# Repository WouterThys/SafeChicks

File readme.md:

# Safe Chicks

Chicks need to be safe so make door go brrrr.

## Ideas/Notes
 - Chord attacked to door and motor winds up/down to open/close door
 - Light sensor 
 - Limit switch -> use the iCab galenus switches? -> magnetic so will not weir out I guess
 - Solar powered?
 - Controller? What I have is:
    - Pico Pi
    - Arduino
    - Raspberry pi 3
    - Beaglebone black
    - Adafruit Huzzah -> has ESP.. 
 - Camera to see if checks are there -> would need raspberry for that (arduino is too lightweight)
 - DC motor
      https://www.farnell.com/datasheets/4376711.pdf?_gl=1*1atfsg3*_gcl_au*MjAyNTY1MDc1NS4xNzQxNjI0NTgy

## Used in V2

### Mouser
426-DRI0044
Fabrik. Artikelnum.: DRI0044
DFRobot 2x1.2A DC Motor Driv / Stroombeheer IC Ontwikkelinghulpmiddelen
TARIC:8473302000 ECCN:EAR99 COO:CN

426-FIT0489-D
Fabrik. Artikelnum.: FIT0489-D
DFRobot Turbo Metal Gear Wor / DFRobo-accessoires
TARIC:8471500090 ECCN:EAR99 COO:CN

653-D2HW-C223MR
Fabrik. Artikelnum.: D2HW-C223MR
Omron Electronics Subminiature Basic S / Basis- / klikschakelaars
TARIC:8536508099 ECCN:EAR99 COO:IT

### RobotShop
RB-Jsu-84 37mm Motor Mount For Titan Series (Pair) 5-4-G 1 1 0 €5.71 €5.71
RB-Sct-941 15T Timing Pinion Pulley (6mm) 02-6-B 1 1 0 €9.45 €9.45
RB-Phi-457 Waterproof Enclosure 200x120x75 w/ Transparent Lid M05-2-D 1 1 0 €13.12 €13.12

## Usefull links
DIY chicken door:
https://davenaves.com/blog/interests-projects/chickens/chicken-coop/arduino-chicken-door/#

Battery management system
https://www.dfrobot.com/product-1714.html

Arduino low power
https://docs.arduino.cc/learn/electronics/low-power/

## Measurements

### POC Arduino Uno (17/03 16:20)
  - added 4[Ohm] resistor between 12V supply
  - Idle ~140mV => 4,9 mW
  - Run  ~1,30V => 423 mW

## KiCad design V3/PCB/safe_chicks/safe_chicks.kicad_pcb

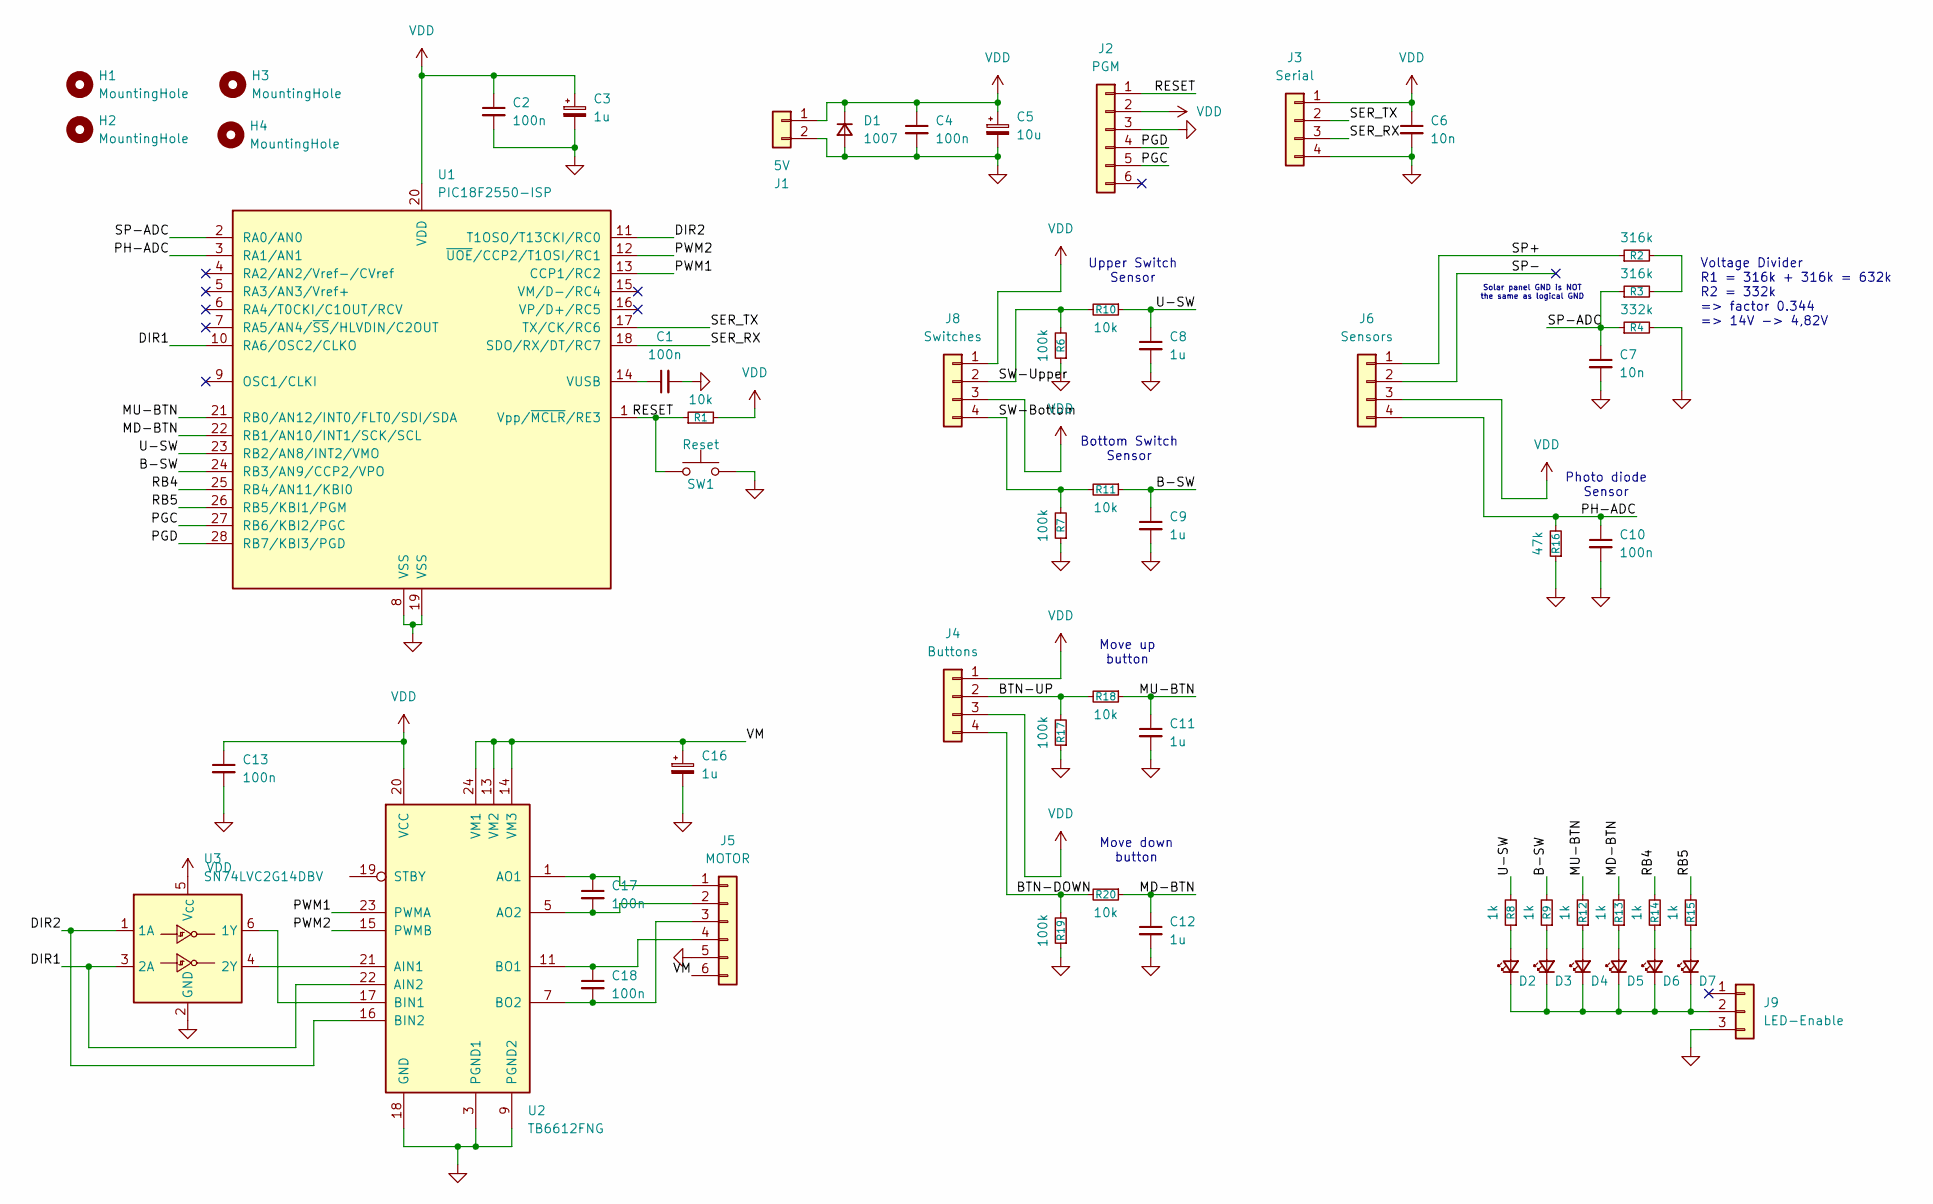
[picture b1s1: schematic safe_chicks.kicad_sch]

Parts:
C1, C2, C4, C10, C13, C17, C18: 100n; C_0603_1608Metric_Pad1.08x0.95mm_HandSolder
C3, C16: 1u; CP_EIA-3216-10_Kemet-I_HandSolder
C5: 10u; CP_EIA-3216-10_Kemet-I_HandSolder
C6, C7: 10n; C_0603_1608Metric_Pad1.08x0.95mm_HandSolder
C8, C9, C11, C12: 1u; C_0603_1608Metric_Pad1.08x0.95mm_HandSolder
D1: 1007; D_DO-15_P10.16mm_Horizontal
D2, D3, D4, D5, D6, D7: LED_Small; LED_0603_1608Metric_Pad1.05x0.95mm_HandSolder
H1, H2, H3, H4: MountingHole; MountingHole_3.2mm_M3_Pad_Via
J1: 5V; TerminalBlock_bornier-2_P5.08mm
J2: PGM; PinHeader_1x06_P2.54mm_Vertical
J3: Serial; Molex_PicoBlade_53047-0410_1x04_P1.25mm_Vertical
J4: Buttons; Molex_PicoBlade_53047-0410_1x04_P1.25mm_Vertical
J5: MOTOR; PinHeader_1x06_P2.54mm_Vertical
J6: Sensors; Molex_PicoBlade_53047-0410_1x04_P1.25mm_Vertical
J8: Switches; Molex_PicoBlade_53047-0410_1x04_P1.25mm_Vertical
J9: LED-Enable; PinHeader_1x03_P2.54mm_Vertical
R1, R10, R11, R18, R20: 10k; R_0603_1608Metric_Pad0.98x0.95mm_HandSolder
R2, R3: 316k; R_0603_1608Metric_Pad0.98x0.95mm_HandSolder
R4: 332k; R_0603_1608Metric_Pad0.98x0.95mm_HandSolder
R6, R7, R17, R19: 100k; R_0603_1608Metric_Pad0.98x0.95mm_HandSolder
R8, R9, R12, R13, R14, R15: 1k; R_0603_1608Metric_Pad0.98x0.95mm_HandSolder
R16: 47k; R_0603_1608Metric_Pad0.98x0.95mm_HandSolder
SW1: Reset; SW_PUSH_6mm_H4.3mm
U1: PIC18F2550-ISP; DIP-28_W7.62mm
U2: TB6612FNG; SSOP-24_5.3x8.2mm_P0.65mm
U3: SN74LVC2G14DBV; SOT-23-6

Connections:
/B-SW: C9.1, R9.2, R11.1, U1.24 (RB3/AN9/CCP2/VPO)
/BTN-DOWN: J4.4, R19.2, R20.2
/BTN-UP: J4.2, R17.2, R18.2
/DIR1: U1.10 (RA6/OSC2/CLKO), U2.22 (AIN2), U3.3 (2A)
/DIR2: U1.11 (T1OSO/T13CKI/RC0), U2.16 (BIN2), U3.1 (1A)
/MD-BTN: C12.1, R13.2, R20.1, U1.22 (RB1/AN10/INT1/SCK/SCL)
/MU-BTN: C11.1, R12.2, R18.1, U1.21 (RB0/AN12/INT0/FLT0/SDI/SDA)
/PGC: J2.5, U1.27 (RB6/KBI2/PGC)
/PGD: J2.4, U1.28 (RB7/KBI3/PGD)
/PH-ADC: C10.1, J6.4, R16.2, U1.3 (RA1/AN1)
/PWM1: U1.13 (CCP1/RC2), U2.23 (PWMA)
/PWM2: U1.12 (~UOE/CCP2/T1OSI/RC1), U2.15 (PWMB)
/RB4: R14.2, U1.25 (RB4/AN11/KBI0)
/RB5: R15.2, U1.26 (RB5/KBI1/PGM)
/RESET: J2.1, R1.1, SW1.1, U1.1 (Vpp/~MCLR/RE3)
/SER_RX: J3.3, U1.18 (SDO/RX/DT/RC7)
/SER_TX: J3.2, U1.17 (TX/CK/RC6)
/SP+: J6.1, R2.1
/SP-: J6.2
/SP-ADC: C7.1, R3.1, R4.1, U1.2 (RA0/AN0)
/SW-Bottom: J8.4, R7.2, R11.2
/SW-Upper: J8.2, R6.2, R10.2
/U-SW: C8.1, R8.2, R10.1, U1.23 (RB2/AN8/INT2/VMO)
/VM: C16.1, J5.6, U2.13 (VM2), U2.14 (VM3), U2.24 (VM1)
GND: C1.2, C2.2, C3.2, C4.2, C5.2, C6.2, C7.2, C8.2, C9.2, C10.2, C11.2, C12.2, C13.2, C16.2, D1.2 (A), J1.2, J2.3, J3.4, J5.5, J9.3, R4.2, R6.1, R7.1, R16.1, R17.1, R19.1, SW1.2, U1.8 (VSS), U1.19 (VSS), U2.3 (PGND1), U2.4 (PGND1), U2.9 (PGND2), U2.10 (PGND2), U2.18 (GND), U3.2 (GND)
unnamed: D2.2 (A), R8.1
unnamed: D2.1 (K), D3.1 (K), D4.1 (K), D5.1 (K), D6.1 (K), D7.1 (K), J9.2
unnamed: D3.2 (A), R9.1
unnamed: D4.2 (A), R12.1
unnamed: D5.2 (A), R13.1
unnamed: D6.2 (A), R14.1
unnamed: D7.2 (A), R15.1
unnamed: C17.1, J5.1, U2.1 (AO1), U2.2 (AO1)
unnamed: C17.2, J5.2, U2.5 (AO2), U2.6 (AO2)
unnamed: C18.2, J5.3, U2.7 (BO2), U2.8 (BO2)
unnamed: C18.1, J5.4, U2.11 (BO1), U2.12 (BO1)
unnamed: R2.2, R3.2
unnamed: C1.1, U1.14 (VUSB)
unnamed: U2.21 (AIN1), U3.4 (2Y)
unnamed: U2.17 (BIN1), U3.6 (1Y)
VDD: C2.1, C3.1, C4.1, C5.1, C6.1, C13.1, D1.1 (K), J1.1, J2.2, J3.1, J4.1, J4.3, J6.3, J8.1, J8.3, R1.2, U1.20 (VDD), U2.20 (VCC), U3.5 (V_{CC})

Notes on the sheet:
Move down button
Solar panel GND is NOT the same as logical GND
Bottom Switch Sensor
Move up button
Photo diode Sensor
Upper Switch Sensor
Voltage Divider R1 = 316k + 316k = 632k R2 = 332k => factor 0.344 => 14V -> 4,82V

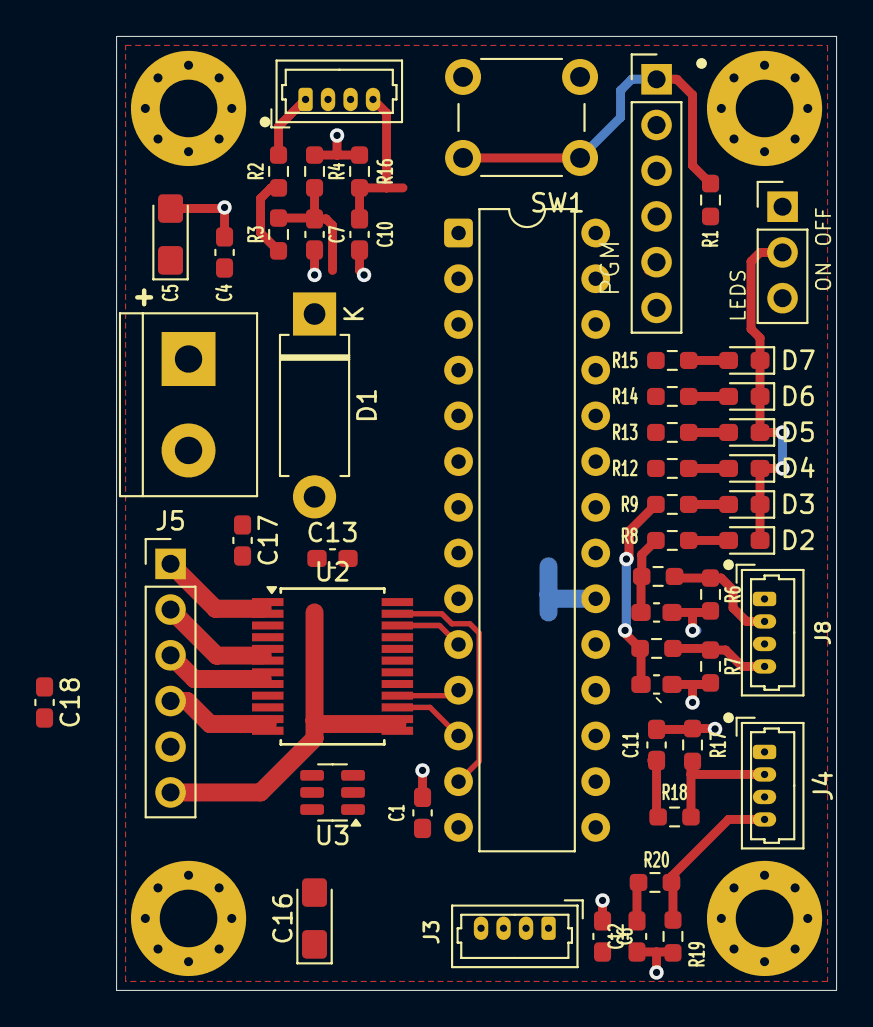
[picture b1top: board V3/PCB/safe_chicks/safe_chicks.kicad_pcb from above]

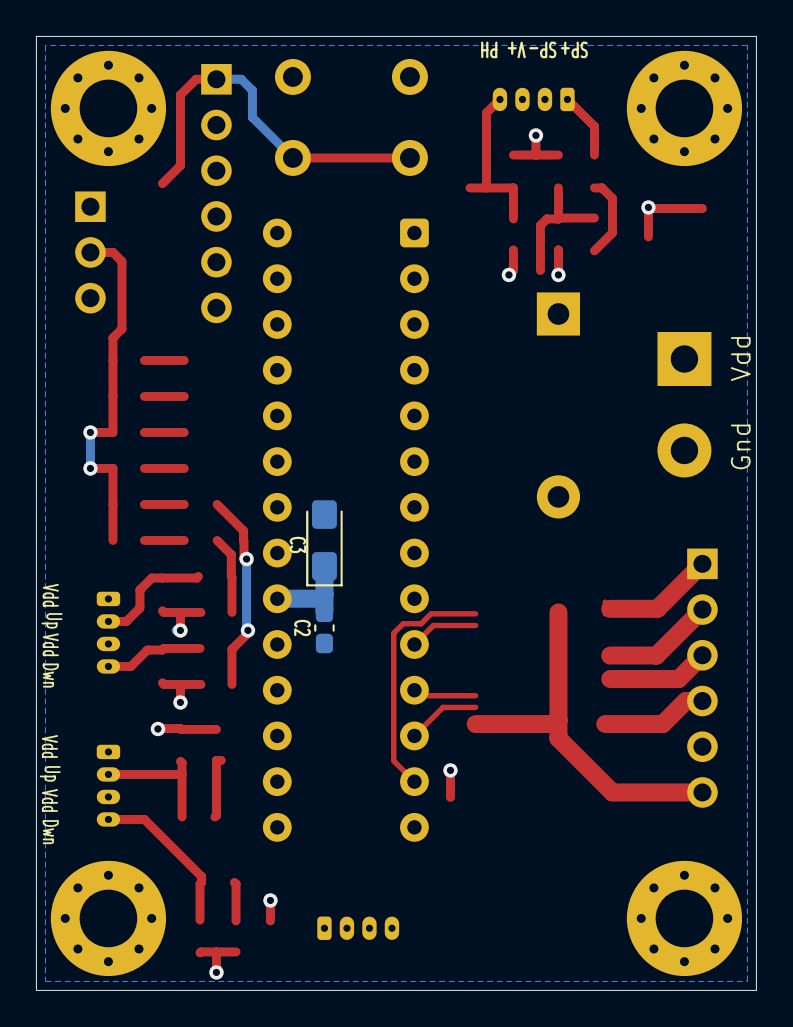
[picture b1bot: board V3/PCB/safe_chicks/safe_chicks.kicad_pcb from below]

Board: 2 copper layers, 40.0 x 53.0 mm, 58 parts (2 on the bottom side), 40 nets.

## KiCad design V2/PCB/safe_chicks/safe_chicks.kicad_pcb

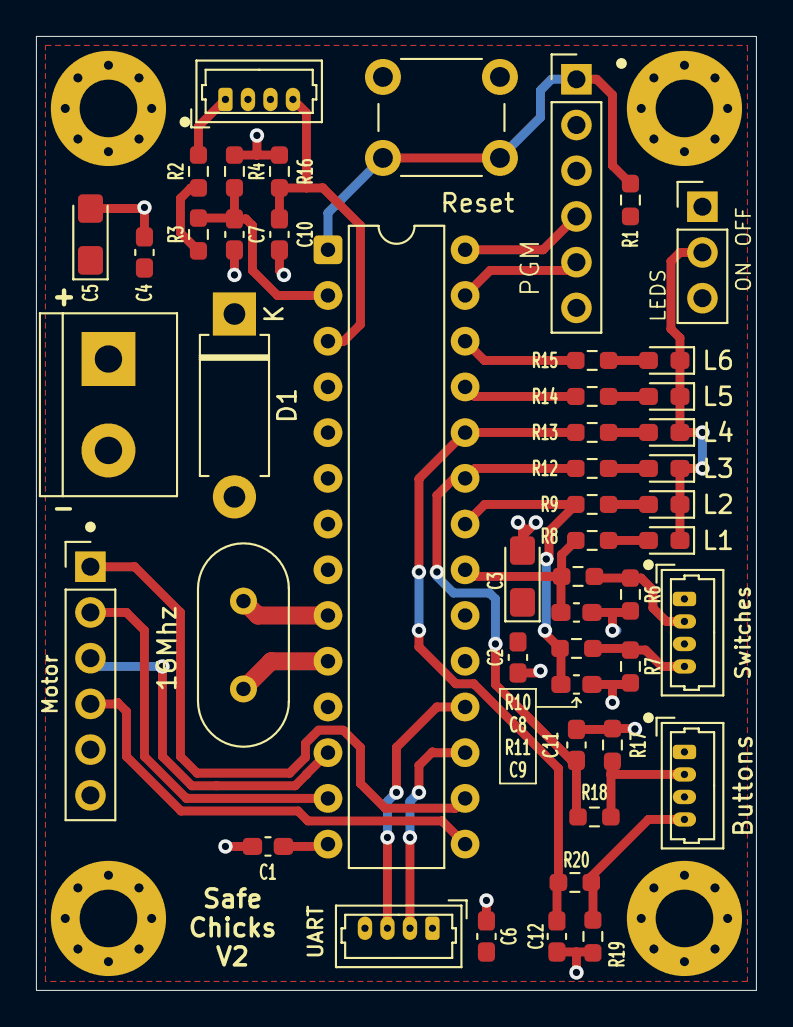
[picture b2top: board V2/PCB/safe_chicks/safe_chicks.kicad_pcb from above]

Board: 2 copper layers, 40.0 x 53.0 mm, 53 parts (0 on the bottom side), 35 nets.

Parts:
16Mhz: 16MHz; Crystal_HC49-U_Vertical
Buttons: Buttons; Molex_PicoBlade_53047-0410_1x04_P1.25mm_Vertical
C1, C2, C4, C10: 100n; C_0603_1608Metric_Pad1.08x0.95mm_HandSolder
C3: 1u; CP_EIA-3216-10_Kemet-I_HandSolder
C5: 10u; CP_EIA-3216-10_Kemet-I_HandSolder
C6, C7: 10n; C_0603_1608Metric_Pad1.08x0.95mm_HandSolder
C8, C9, C11, C12: 1u; C_0603_1608Metric_Pad1.08x0.95mm_HandSolder
D1: 1007; D_DO-15_P10.16mm_Horizontal
H1, H2, H3, H4: MountingHole; MountingHole_3.2mm_M3_Pad_Via
J1: 5V; TerminalBlock_bornier-2_P5.08mm
J2: PGM; PinHeader_1x06_P2.54mm_Vertical
J6: Sensors; Molex_PicoBlade_53047-0410_1x04_P1.25mm_Vertical
J9: LED-Enable; PinHeader_1x03_P2.54mm_Vertical
L1, L2, L3, L4, L5, L6: LED_Small; LED_0603_1608Metric_Pad1.05x0.95mm_HandSolder
Motor: MTR; PinHeader_1x06_P2.54mm_Vertical
R1, R10, R11, R18, R20: 10k; R_0603_1608Metric_Pad0.98x0.95mm_HandSolder
R2, R3: 613k; R_0603_1608Metric_Pad0.98x0.95mm_HandSolder
R4: 332k; R_0603_1608Metric_Pad0.98x0.95mm_HandSolder
R6, R7, R17, R19: 100k; R_0603_1608Metric_Pad0.98x0.95mm_HandSolder
R8, R9, R12, R13, R14, R15: 1k; R_0603_1608Metric_Pad0.98x0.95mm_HandSolder
R16: 47k; R_0603_1608Metric_Pad0.98x0.95mm_HandSolder
Reset: Reset; SW_PUSH_6mm_H4.3mm
Switches: Switches; Molex_PicoBlade_53047-0410_1x04_P1.25mm_Vertical
U1: PIC18F2550-ISP; DIP-28_W7.62mm
UART: Serial; Molex_PicoBlade_53047-0410_1x04_P1.25mm_Vertical

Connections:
/B-SW: C9.1, R9.2, R11.1, U1.22 (RB1/AN10/INT1/SCK/SCL)
/BTN-DOWN: Buttons.4, R19.2, R20.2
/BTN-UP: Buttons.2, R17.2, R18.2
/DIR1: Motor.1, U1.16 (VP/D+/RC5)
/DIR2: Motor.4, U1.15 (VM/D-/RC4)
/MD-BTN: C12.1, R13.2, R20.1, U1.24 (RB3/AN9/CCP2/VPO)
/MU-BTN: C11.1, R12.2, R18.1, U1.23 (RB2/AN8/INT2/VMO)
/PGC: J2.5, U1.27 (RB6/KBI2/PGC)
/PGD: J2.4, U1.28 (RB7/KBI3/PGD)
/PH-ADC: C10.1, J6.4, R16.2, U1.3 (RA1/AN1)
/PWM1: Motor.2, U1.13 (CCP1/RC2)
/PWM2: Motor.3, U1.12 (~UOE/CCP2/T1OSI/RC1)
/RB4: R14.2, U1.25 (RB4/AN11/KBI0)
/RB5: R15.2, U1.26 (RB5/KBI1/PGM)
/RESET: J2.1, R1.1, Reset.1, U1.1 (Vpp/~MCLR/RE3)
/SER_RX: U1.18 (SDO/RX/DT/RC7), UART.3
/SER_TX: U1.17 (TX/CK/RC6), UART.2
/SP+: J6.1, R2.1
/SP-ADC: C7.1, R3.1, R4.1, U1.2 (RA0/AN0)
/SW-Bottom: R7.2, R11.2, Switches.4
/SW-Upper: R6.2, R10.2, Switches.2
/U-SW: C8.1, R8.2, R10.1, U1.21 (RB0/AN12/INT0/FLT0/SDI/SDA)
GND: C1.2, C2.2, C3.2, C4.2, C5.2, C6.2, C7.2, C8.2, C9.2, C10.2, C11.2, C12.2, D1.2 (A), J1.2, J2.3, J9.3, Motor.5, R4.2, R6.1, R7.1, R16.1, R17.1, R19.1, Reset.2, U1.8 (VSS), U1.19 (VSS), UART.4
unnamed: L1.2 (A), R8.1
unnamed: J9.2, L1.1 (K), L2.1 (K), L3.1 (K), L4.1 (K), L5.1 (K), L6.1 (K)
unnamed: L2.2 (A), R9.1
unnamed: L3.2 (A), R12.1
unnamed: L4.2 (A), R13.1
unnamed: L5.2 (A), R14.1
unnamed: L6.2 (A), R15.1
unnamed: R2.2, R3.2
unnamed: 16Mhz.1, U1.9 (OSC1/CLKI)
unnamed: 16Mhz.2, U1.10 (RA6/OSC2/CLKO)
unnamed: C1.1, U1.14 (VUSB)
VDD: Buttons.1, Buttons.3, C2.1, C3.1, C4.1, C5.1, C6.1, D1.1 (K), J1.1, J2.2, J6.3, Motor.6, R1.2, Switches.1, Switches.3, U1.20 (VDD), UART.1

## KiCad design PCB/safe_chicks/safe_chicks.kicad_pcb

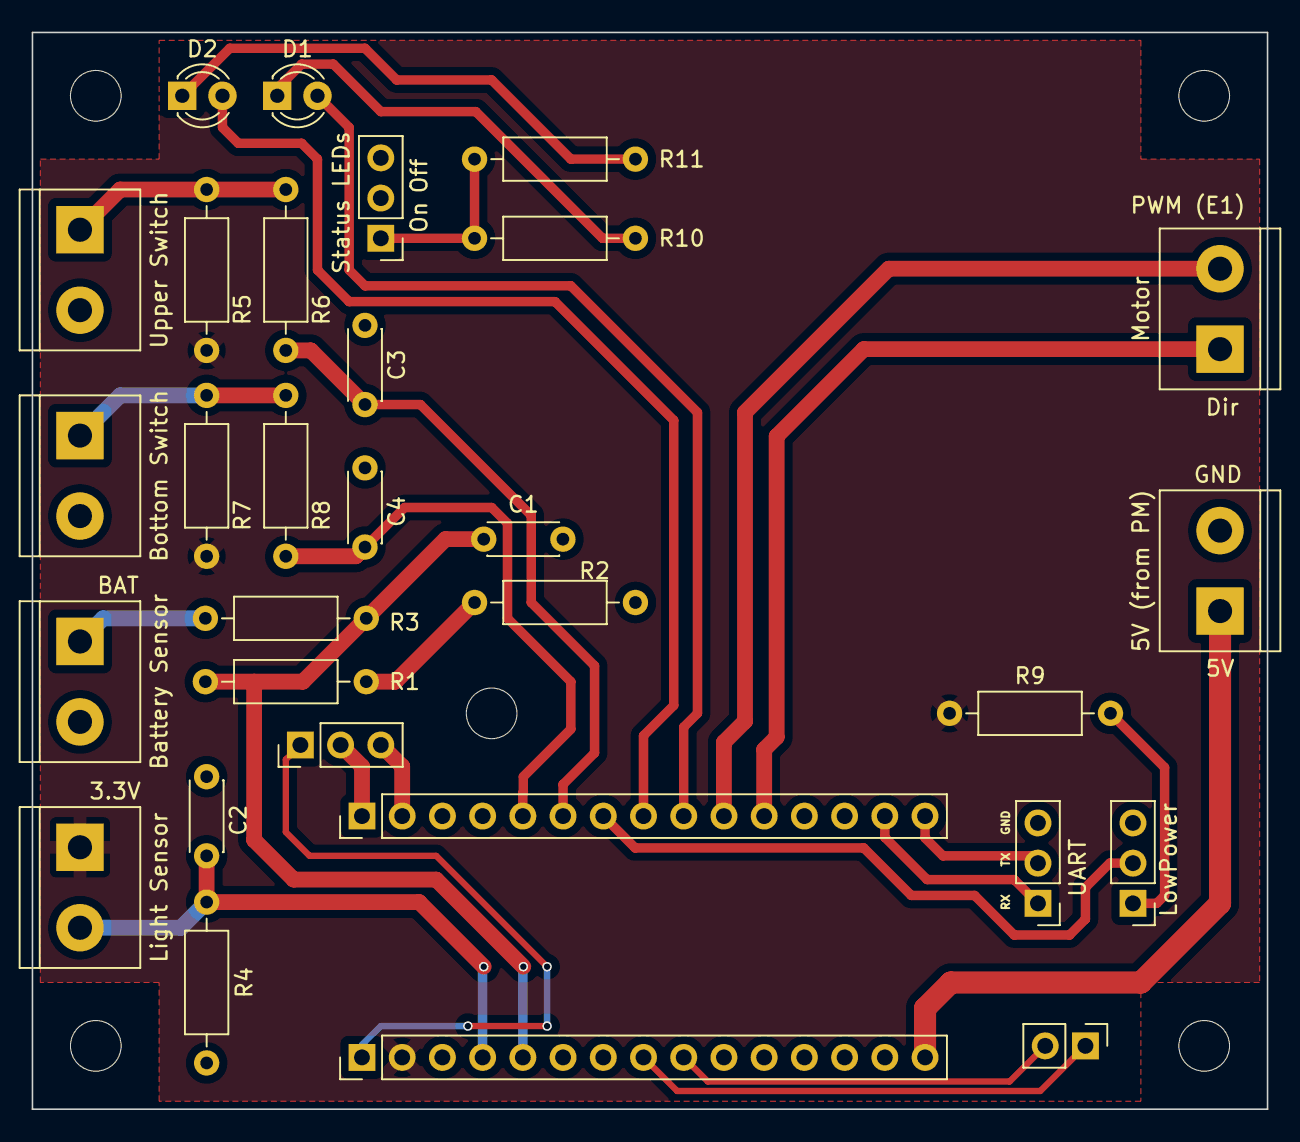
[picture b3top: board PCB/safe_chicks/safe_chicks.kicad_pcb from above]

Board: 2 copper layers, 78.0 x 68.0 mm, 35 parts (0 on the bottom side), 27 nets.

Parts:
C1, C2: 100n; C_Disc_D4.3mm_W1.9mm_P5.00mm
C3, C4: 1u; C_Disc_D4.3mm_W1.9mm_P5.00mm
D1, D2: LED; LED_D3.0mm
H1, H2, H3, H4, H5: MountingHole; MountingHole_3.2mm_M3
J1, J2: Conn_01x15; PinHeader_1x15_P2.54mm_Vertical
J3: Battery Sensor; TerminalBlock_bornier-2_P5.08mm
J4: Light Sensor; TerminalBlock_bornier-2_P5.08mm
J5: Upper Switch; TerminalBlock_bornier-2_P5.08mm
J6: Bottom Switch; TerminalBlock_bornier-2_P5.08mm
J7: Motor; TerminalBlock_bornier-2_P5.08mm
J8: 5V (from PM); TerminalBlock_bornier-2_P5.08mm
J9: LowPower; PinHeader_1x03_P2.54mm_Vertical
J10: Status LEDs; PinHeader_1x03_P2.54mm_Vertical
J11: UART; PinHeader_1x03_P2.54mm_Vertical
J12: SPI; PinHeader_1x03_P2.54mm_Vertical
J13: Conn_01x02; PinHeader_1x02_P2.54mm_Vertical
R1, R2, R3: 1M; R_Axial_DIN0207_L6.3mm_D2.5mm_P10.16mm_Horizontal
R4: 47k; R_Axial_DIN0207_L6.3mm_D2.5mm_P10.16mm_Horizontal
R5, R6, R7, R8, R9: 100k; R_Axial_DIN0207_L6.3mm_D2.5mm_P10.16mm_Horizontal
R10, R11: 220; R_Axial_DIN0207_L6.3mm_D2.5mm_P10.16mm_Horizontal

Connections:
+3V3: J1.2, J4.1, R5.1, R7.1, R9.1
/*D3: J2.10, J7.2
/*D5: D2.2 (A), J2.8
/*D6: J2.7, J9.2
/*D11/MOSI: J2.2, J12.3
/A0: C2.1, J1.4, J4.2, R4.1
/A1: C1.1, J1.5, R1.1, R3.2
/A4/SDA: J1.8, J13.1
/A5/SCL: J1.9, J13.2
/D0/RX: J2.14, J11.1
/D1/TX: J2.15, J11.2
/D2: J2.11, J7.1
/D4: D1.2 (A), J2.9
/D7: C3.1, J2.6, R6.2
/D8: C4.1, J2.5, R8.2
/D12/MISO: J2.1, J12.2
/D13/SCK: J1.1, J12.1
GND: C1.2, C2.2, C3.2, C4.2, J1.14, J2.12, J3.2, J5.2, J6.2, J8.2, J9.3, J10.2, J11.3, R2.2, R4.2
unnamed: D1.1 (K), R10.1
unnamed: D2.1 (K), R11.1
unnamed: J3.1, R3.1
unnamed: J5.1, R5.2, R6.1
unnamed: J6.1, R7.2, R8.1
unnamed: J9.1, R9.2
unnamed: J10.1, R10.2, R11.2
unnamed: R1.2, R2.1
VCC: J1.15, J8.1

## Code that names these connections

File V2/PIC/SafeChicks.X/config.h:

#ifndef CONFIG_H
#define	CONFIG_H

#include <xc.h> // include processor files - each processor file is guarded.  

#define _XTAL_FREQ 1000000UL /* 1 MHz clock */
#define DEBUG_MODE 0

#define PRIu8 "hhu"
#define PRId8 "hhd"
#define PRIx8 "hhx"
#define PRIu16 "hu"
#define PRId16 "hd"
#define PRIx16 "hx"
#define PRIu32 "lu"
#define PRId32 "dl"
#define PRIx32 "x"
#define PRIu64 "llu" // or possibly "lu"
#define PRId64 "lld" // or possibly "ld"
#define PRIx64 "llx" // or possibly "lx"


/*******************************************************************************
 *                      PIN MAPPING 
 ******************************************************************************/

/* This file contains all pin mapping of the board */
#define MOTOR_PWM_Pin   PORTCbits.RC2     // Pin for motor PWM
#define MOTOR_DIR_Pin   PORTCbits.RC1     // Pin for motor direction
#define MOTOR_DIR_Dir   TRISCbits.RC1     // Pin for motor direction

// Switched and buttons
/* Button up */
#define U_BUTTON_Pin    PORTBbits.RB0
#define U_BUTTON_Dir    TRISBbits.TRISB0
/* Button down */
#define D_BUTTON_Pin    PORTBbits.RB1
#define D_BUTTON_Dir    TRISBbits.TRISB1
/* Limit switch as a fail safe */
#define L_SWITCH_Pin    PORTBbits.RB3
#define L_SWITCH_Dir    TRISBbits.TRISB3

// LEDs
#define LED_BLUE_Pin    PORTBbits.RB4
#define LED_BLUE_Dir    TRISBbits.TRISB4
#define LED_RED_Pin     PORTBbits.RB5
#define LED_RED_Dir     TRISBbits.TRISB5

// Ports for UART
#define UART_TX         PORTCbits.RC7
#define UART_RX         PORTCbits.RC6
    
#define UART_TX_Dir     TRISCbits.TRISC7
#define UART_RX_Dir     TRISCbits.TRISC6

/*******************************************************************************
 *                      ERROR CODES 
 ******************************************************************************/
const uint8_t   ERROR_LIMIT_SWITCH_CLOSED = 1;
const uint8_t   ERROR_SENSORS_UP_WHILE_NIGHT = 2;
const uint8_t   ERROR_SENSORS_DOWN_WHILE_DAY = 4;
const uint8_t   ERROR_MOTOR_RUN_TOO_LONG = 8;

/*******************************************************************************
 *                      THRESHOLD VALUES 
 ******************************************************************************/
#define SECONDS_IN_MINUTE 60
#define MILLIS_IN_SECOND  1000

/* Threshold used to switch from day->night (sensor is max 1023) */
#define DAY_THRESHOLD     200
#define NIGHT_THRESHOLD   200

#define SLEEP_COUNT   5   /* The total sleep time will be SLEEP_TIME_MS times this value, to allow shorter wakeup intervals for sanity checking */
#define DAY_COUNT     3   /* Hysteresis counter, depending on time between sleeps this makes how long day/night should be read before changing */

/*******************************************************************************
 *                      MOTOR SETTINGS 
 ******************************************************************************/
#define CCW_DIRECTION       0   /* Counter clockwise direction                */
#define CW_DIRECTION        1   /* Clockwise direction                        */

#define MOTOR_FULL_SPEED    70  /* PWM percentage                             */
#define MOTOR_HALF_SPEED    35  /* PWM percentage                             */

#define MOTOR_DOWN_FULL_CNT 1100/* The max count the motor will run fast.     */
#define MOTOR_DOWN_SLOW_CNT 400 /* The max count the motor will run slow.     */
#define MAX_MOTOR_COUNT     (3*(MOTOR_DOWN_FULL_CNT + MOTOR_DOWN_SLOW_CNT))


/*******************************************************************************
 *                      SERIAL SETTINGS 
 ******************************************************************************/

/**
 * Baud rate of serial communication
 */
#define SERIAL_BAUD 1200



#endif	/* CONFIG_H */

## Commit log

2025-03-17 Some first setup
2025-03-17 Create FSM
2025-03-17 Motor dimensions
2025-03-22 FSM done I think
2025-03-31 Remove files which should not be in git
2025-03-31 Add first PCB
2025-03-31 Analyse log files with python script
2025-03-31 update pcb
2025-03-31 Created PCB
2025-04-19 twerkt
2025-04-19 add some test programs to finetune sensors and delays
2025-04-19 test motor
2025-04-20 more config
2025-04-20 faster motor start and stop
2025-04-20 motor delays
2025-04-21 Do not run door when it is not needed
2025-04-21 Use longer start up time after all
2025-05-29 Run the motor a little slower, only check low power pin iso debug flag
2025-06-14 Very small changes and also add python tkinter GUI to debug the state
2025-06-14 Slow down motor a litte to 50%
2025-08-18 Make ready for V2
2025-08-19 Create V2 PCB and test solar panel
2025-08-22 More on PCB V2
2025-08-26 First try of the mplab project
2025-08-26 Internal OSC and T0 testing with interrupts WORKS
2025-08-26 First setup of the motor
2025-08-28 Move around file names
2025-08-28 Setting up the FSM
2025-08-29 FSM is working with buttons and motor runs
2025-09-01 This works but sensors could be better
2025-09-02 Some ideas on PCB V3
2025-09-02 Setting motor speeds to finetune
2025-09-02 It works now also with sleep mode
2025-09-02 Now with interrupts on the button up pin
2025-09-02 Move button pins so they can be used for interrupts
2025-09-04 Add vscode config
2025-09-04 print FSM state every time before going to sleep. Add script to analyse
2025-09-04 Cleaner debugging with sensors
2025-09-05 I think we are ready
2025-09-06 done
2025-09-07 Done* with oher stop
2025-11-29 Added parts to readme
2025-12-04 Add test code
2025-12-04 mplab config
2025-12-31 Setup summer 2025
2025-12-31 Changes on pc...
2025-12-31 Increase closing time and add night fake when both buttons are pushed
2025-12-31 Config december 2025
